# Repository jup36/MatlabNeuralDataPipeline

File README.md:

# MatlabNeuralDataPipeline
This repo contains the pipeline for Matlab neural data analysis. 
This repo aims to include all neural data analysis codes in applicable/generalizable forms.
Please see, the associated github repository, https://github.com/jup36/MatlabNeuralDataPipeline.git

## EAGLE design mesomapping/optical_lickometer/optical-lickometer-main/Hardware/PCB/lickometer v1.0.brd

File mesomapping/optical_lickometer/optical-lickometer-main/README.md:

## General description

This repository contains the design files for the assembly of a high-precision optical fiber based lickometer for mice.

----

## Features

* Fiber optic based lickometer
* Dual detection of licks and pokes
* TTL outputs
* Embedded poke LED 
* Support for a low profile solenoid valve
* RJ jack connector and screw terminal interface

----

## Folder structure

    .
    ├── Bonsai                  # Bonsai workflows
    ├── Hardware                # Design files
    │   ├── CAD                 # Mechanical design files, BOM and assembly instructions
    │   └── PCB                 # Schematic, layout and BOM of electronic board

----

## Licensing

License files can be found, and are applied to, each individual subfolder in this repository.

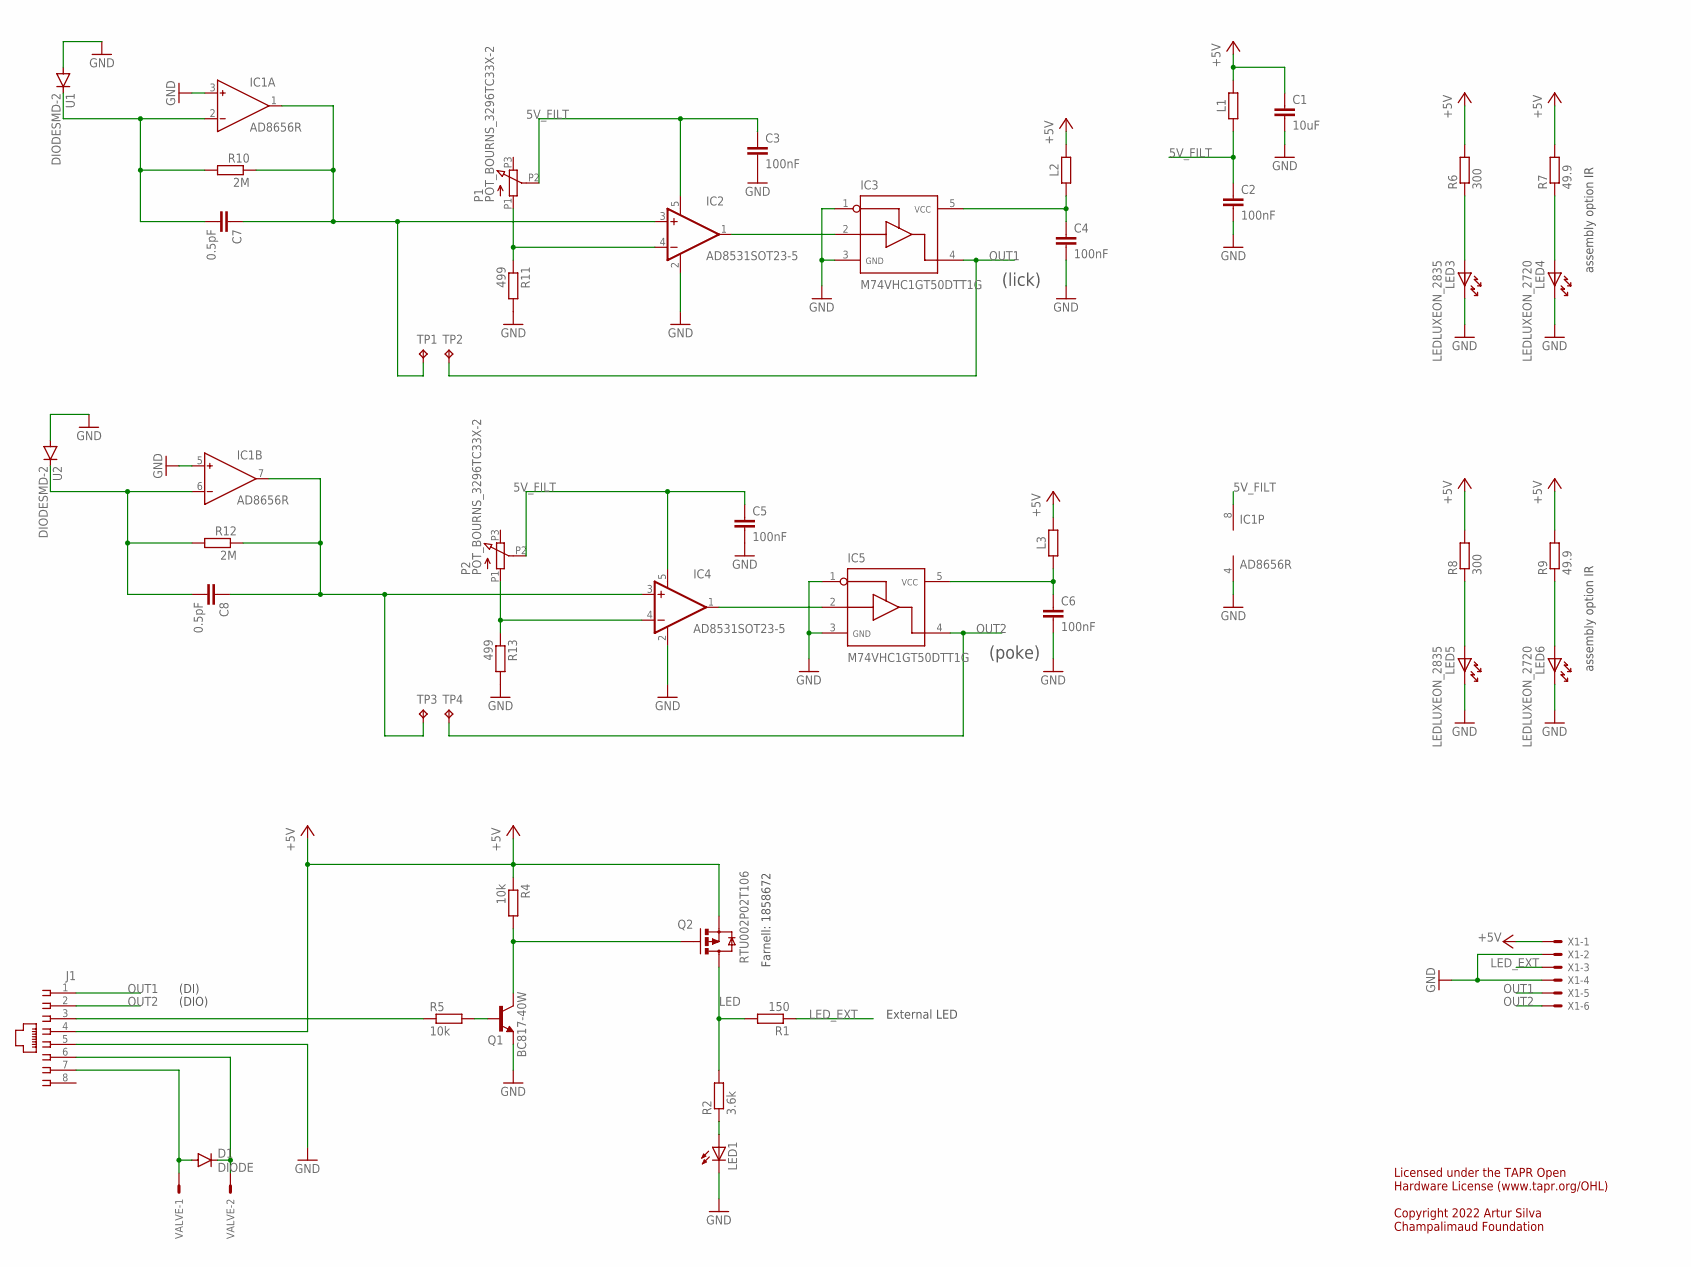
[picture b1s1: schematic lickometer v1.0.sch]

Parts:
C1: 10uF; C0603
C2, C3, C4, C5, C6: 100nF; C0402
C7, C8: 0.5pF; C0402
D1: DIODE; SOD-323-DIODE
IC1: AD8656R; SO8
IC2, IC4: AD8531SOT23-5; SOT23-5
IC3, IC5: M74VHC1GT50DTT1G; SOT23-5
J1: 215878-2
L1, L2, L3: 1k@100M; R0402
LED1: LED3MM
LED3, LED5: LEDLUXEON_2835; LED_LUXEON_2835
LED4, LED6: LEDLUXEON_2720; LED_LUXEON_2720
P1, P2: POT_BOURNS_3296TC33X-2; POT-TC33X-2
Q1: BC817-40W; SOT323-BEC
Q2: RTU002P02T106; SOT323
R1: 150; R0402
R2: 3.6k; R0402
R4, R5: 10k; R0402
R6, R8: 300; R0805
R7, R9: 49.9; R0805
R10, R12: 2M; R0402
R11, R13: 499; R0402
TP1, TP2, TP3, TP4: TPTP08SQ; TP08SQ
U1, U2: DIODESMD-2; SMD-2
VALVE: 22-23-2021
X1: 22-23-2061

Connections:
5V_FILT: C2.1, C3.1, C5.1, IC1.8 (V+), IC2.5 (V+), IC4.5 (V+), L1.2, P1.P2 (S), P2.P2 (S)
+5V: C1.1, J1.4, L1.1, L2.2, L3.2, Q2.1 (S), R4.1, R6.2, R7.2, R8.2, R9.2, X1.1
GND: C1.2, C2.2, C3.2, C4.2, C5.2, C6.2, IC1.3 (IN+), IC1.4 (V-), IC1.5 (IN+), IC2.2 (V-), IC3.1, IC3.3, IC4.2 (V-), IC5.1, IC5.3, J1.5, LED1.K (C), LED3.KATHODE (K), LED4.KATHODE (K), LED5.KATHODE (K), LED6.KATHODE (K), Q1.E, R11.2, R13.2, U1.A, U2.A, X1.2, X1.4
IN1: IC4.4 (-IN), P2.P1 (A), R13.1
IN2: IC2.4 (-IN), P1.P1 (A), R11.1
LED: Q2.3 (D), R1.2, R2.2
LED_EXT: R1.1, X1.3
unnamed: LED3.ANODE (A), R6.1
unnamed: C4.1, IC3.5, L2.1
unnamed: C7.2, IC1.2 (IN-), R10.2, U1.C
unnamed: D1.A, J1.7, VALVE.1
unnamed: D1.C, J1.6, VALVE.2
unnamed: IC2.1 (OUT), IC3.2
unnamed: J1.3, R5.1
unnamed: C7.1, IC1.1 (OUT), IC2.3 (+IN), R10.1, TP1.TP
unnamed: LED4.ANODE (A), R7.1
unnamed: IC4.1 (OUT), IC5.2
unnamed: C6.1, IC5.5, L3.1
unnamed: LED1.A, R2.1
unnamed: C8.2, IC1.6 (IN-), R12.2, U2.C
unnamed: C8.1, IC1.7 (OUT), IC4.3 (+IN), R12.1, TP3.TP
unnamed: LED5.ANODE (A), R8.1
unnamed: Q1.C, Q2.2 (G), R4.2
unnamed: Q1.B, R5.2
unnamed: LED6.ANODE (A), R9.1
OUT1: IC3.4, J1.1, TP2.TP, X1.5
OUT2: IC5.4, J1.2, TP4.TP, X1.6

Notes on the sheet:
External LED
Farnell: 1858672
Licensed under the TAPR Open Hardware License (www.tapr.org/OHL) Copyright 2022 Artur Silva Champalimaud Foundation
(lick)
(poke)
assembly option IR
(DIO)
(DI)

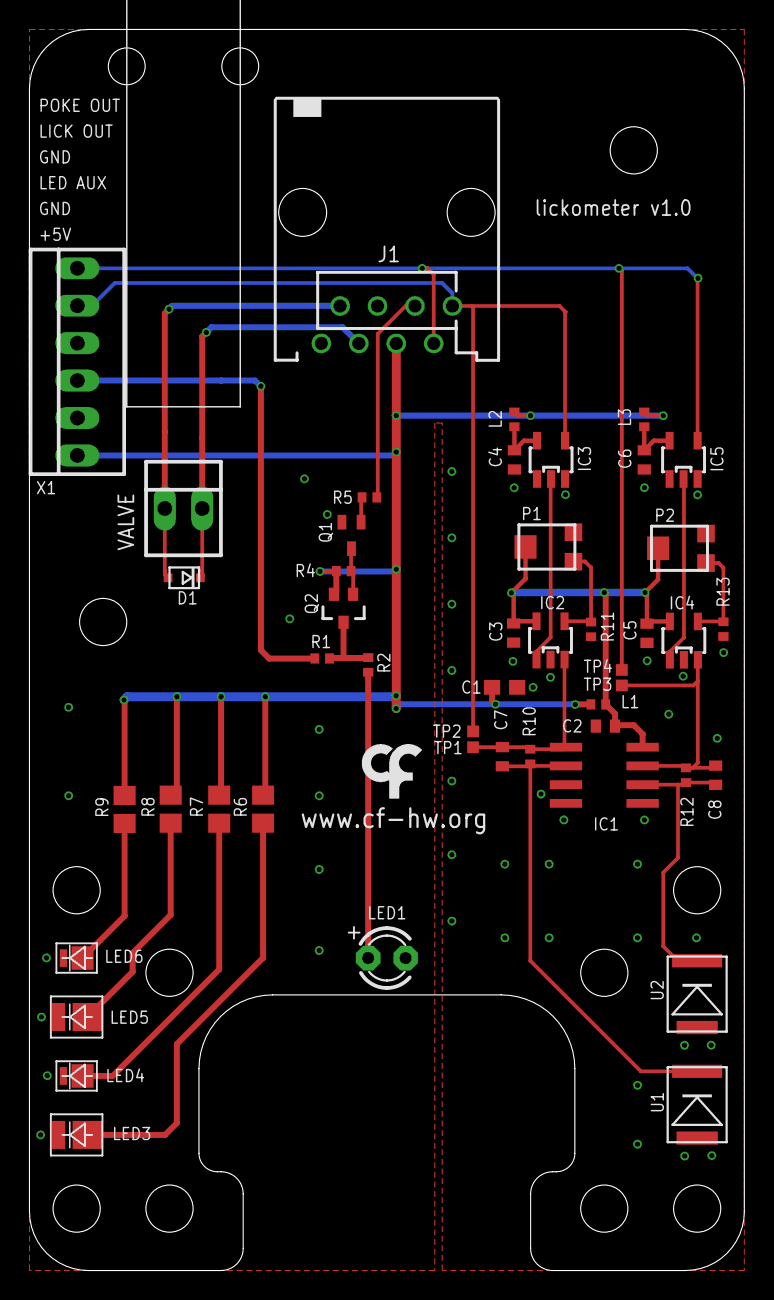
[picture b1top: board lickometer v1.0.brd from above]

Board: 2 copper layers, 48.5 x 84.2 mm, 49 parts (1 on the bottom side), 27 nets.

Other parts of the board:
U$1: LOGO_5
U$2: LOGO_7

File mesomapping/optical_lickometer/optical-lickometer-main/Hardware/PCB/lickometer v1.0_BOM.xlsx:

| Part(s) | Quantity | Description | Distributor | Part. No. | Price/Unit | Total Price
 | IC1 | 1 | OPAMP 28MHz 8/SOIC dual | Digikey | AD8656ARZ-REEL7 | 3.66 | 3.66
 | IC2, IC4 | 2 | OPAMP 3MHz SC70-5 | Mouser | AD8531AKSZ-REEL7 | 1.01 | 2.02
 | IC3, IC5 | 2 | Buffer single non-inverting TTL | Digikey | M74VHC1GT50DTT1G | 0.39 | 0.78
 | Q1 | 1 | Transistor BJT NPN SOT-23-3 | Mouser | 621-BC817-40W-7 | 0.27100000000000002 | 0.27100000000000002
 | Q2 | 1 | Transistor MOSFET P-channel SOT-323-3 20V 2.5A | Mouser | 621-DMP2165UW-7 | 0.38500000000000001 | 0.38500000000000001
 | D1 | 1 | Schottky diode 30V 1A SOD323 | Mouser | 621-SDM100K30L-7 | 0.438 | 0.438
 | P1, P2 | 2 | Trimmer 20kΩ 0.5W | Mouser | 652-TC33X-2-203E | 0.23599999999999999 | 0.47199999999999998
 | U1, U2 | 2 | PIN Photodiode SMT | Mouser | 720-SFH2200 | 0.95399999999999996 | 1.9079999999999999
 | R1 | 1 | Resistor SMD 150Ω ±1% 0402 | Mouser | 667-ERJ-2RKF1500X | 8.7999999999999995E-2 | 8.7999999999999995E-2
 | R2 | 1 | Resistor SMD 3,6kΩ ±1% 0402 | Mouser | 667-ERJ-2RKF3601X | 9.0999999999999998E-2 | 9.0999999999999998E-2
 | R7 (IR) | 1 | Resistor SMD 150Ω ±1% 0805 | Mouser | 667-ERJ-6RBD1500V | 0.155 | 0.155
 | R9 (IR) | 1 | Resistor SMD 49,9Ω ±1% 0805 | Mouser | 667-ERJ-6RED49R9V | 0.155 | 0.155
 | R11, R13 | 2 | Resistor SMD 499Ω ±1% 0402 | Mouser | 667-ERJ-2RKF4990X | 8.7999999999999995E-2 | 0.17599999999999999
 | R4, R5 | 2 | Resistor SMD 10kΩ ±1% 0402 | Mouser | 667-ERJ-2RKF1002X | 8.7999999999999995E-2 | 0.17599999999999999
 | R10, R12 | 2 | Resistor SMD 2MΩ ±1% 0402 | Mouser | 71-CRCW04022M00FKEDC | 8.7999999999999995E-2 | 0.17599999999999999
 | L1, L2, L3 | 3 | Ferrite bead 1kΩ 0402 | Mouser | 810-MMZ1005S102CT000 | 8.7999999999999995E-2 | 0.26400000000000001
 | C7, C8 | 2 | Capacitor ceramic 0.5pF 50V C0G/NP0 0402 | Mouser | 81-GRM1555C1HR50WA1D | 0.105 | 0.21
 | C2, C3, C4, C5, C6 | 5 | Capacitor ceramic 100nF 16V ±10% X7R 0402 | Mouser | GCM155R71C104KA55D | 8.7999999999999995E-2 | 0.43999999999999995
 | C1 | 1 | Capacitor ceramic 10uF 10V ±10% X5R 0603 | Mouser | 81-GRM188R61A106KE9D | 0.184 | 0.184
 | LED1 | 1 | LED white T-1 (3MM) | Mouser | 828-OVLAW4CB7 | 0.38500000000000001 | 0.38500000000000001
 | LED4, LED6 (IR) | 2 | Infrared LED 2720 940nm | Mouser | 997-L1IG094000000 | 2.2000000000000002 | 4.4000000000000004
 | VALVE | 1 | Terminal block 2P side entry 2.54mm | Mouser | 571-282834-2 | 1.58 | 1.58
 | J1 | 1 | Ethernet 8P8C top entry | Mouser | 571-55202594 | 1.56 | 1.56
 | X1 | 1 | Teminal block 8P side entry 2.54mm | Mouser | 571-282834-6 | 4.78 | 4.78
 |  | 1 | Printed Circuit Board | Seeedstudio |  | 5 | 5
 | Components | 40
 |  |  |  |  |  | Total | 22.200000000000003

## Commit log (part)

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2017-11-07 Matlab code to simulate a synfire chain network
    Synfire chain network:
    http://www.scholarpedia.org/article/Synfire_chains
    https://www.mathworks.com/matlabcentral/fileexchange/13802-synfire
    Pehlevan_Olveczky_2017
2018-02-21 SpikePreprocessing codes added
2018-02-22 SpikePreprocessing files updated 2/22/18
2018-03-09 adding behaviorTimestamps
2018-03-24 adding MVGC
2018-03-24 adding chronux
2018-03-24 adding multiple functions
2018-03-25 adding GC
2018-03-30 adding new joystick scripts/functions
2018-04-02 editing behaviorTimestamps.m
2018-05-01 update050118
2018-05-01 addingGPFA
2018-05-18 editing old joystick behavioral codes
2018-05-19 adding runGPFA.m getUnitOfHighXcorr.m
2018-07-10 adding fitrm_ranova_multcompare.m
2018-07-26 .adding a bunch of codes
2018-07-26 .adding JRCLUST
2018-07-26 .adding a bunch
2018-07-26 reorganizing the folder
2018-07-26 adding tonic-master
2018-07-26 adding joystickCodes
2018-08-03 editing corrNeuralTrajMovKinematics
2018-08-17 updating from parkj mac
2018-08-23 adding VTA_Cell_classification_to_AGB
2018-08-23 adding func_GMM to VTA_Cell_classification
2018-09-04 adding miscellaneous changes
2018-09-04 small change in behaviorTimestamps.m
2018-09-06 up-to-date ver. before making changes in PSTH_raster and its subfunctions.
2018-09-12 adding spikeSorting auxiliary
2018-09-16 adding behaviorCode for AGB
2018-09-24 just a regular commit
2018-10-10 adding js2.0_Beh
2018-10-29 a bunch of updates
2018-11-02 updating Js2.0 trajectory analysis codes
2018-11-07 updating js2.0 from labbenchmachine
2018-11-12 updating js2.0_Beh from labBench machine
2018-11-12 updating jsBeh2.0 from the lab bench machine
2018-11-16 updating Js2.0 codes from mac
2018-11-20 updating js2.0_Beh from the lab bench PC
2018-11-28 update from lab bench machine
2018-11-29 Important js2.0 code updates including vidoe file process from LabBenchMachine
2018-11-30 updating jsVideoProcess.m from lab bench machine
2018-12-06 updating from labbench PC
2018-12-12 updating from laptop
2019-01-29 updating from the lab bench machine
2019-02-26 update from myrig
2019-03-04 Create getHH3geom
2019-03-04 Create PSTH_rasters_Cg
2019-03-04 Create parse_input_psth_Cg
2019-03-04 updating from the lab bench
2019-03-06 Update behaviorTimestampsJsWrapper.m from myRig
2019-03-06 updating from the labBench
2019-03-06 updating from labBench
2019-03-09 Update PSTH_rasters.m
    Addition of reward PSTHs no-stim trials only.
    Saving spikeTimes cells.
2019-03-12 update from myRecordingRig
2019-04-10 paser_input_Js updated
2019-04-10 updatedFromMyRig
2019-04-10 updating behaviorTimeStampsJsWrapper
2019-04-11 updating JsVideoFileOrganizer
2019-04-11 updating behaviorTimestampsJs
2019-04-11 updating behaviorTimestampsJs.m
2019-04-15 updating from myMac
2019-04-15 JsVideoFileOrganizer
2019-04-15 commiting JsVideoFileOrganizer
2019-04-30 Editing behaviorTimestampsJs on 4/30/19
2019-05-01 Editing behaviorTimestampsJs on 5/1/19
2019-06-07 updating from myRig
2019-07-31 updating from my mac
2019-08-14 Adding cgStimEffectAnalysisJsTrj.m
2019-08-20 updating behaviorTimestampsJs.m from my Rig'
2019-09-10 updating changes from the labBench
2019-09-10 updating from my labtop
2019-10-29 update from my laptop
2019-10-29 updating from labbench mostly hand trajectory preprocessing stuffs
2019-10-30 updating handtrajectory stuffs from labBench machine
2019-11-02 update from labBench
2019-11-02 update from myRig on videoHandTrajAnalysis
2019-11-05 update from the labBench
2019-11-07 update from Mac
2019-11-08 updating at labBench
2019-11-12 updating from labBench for 'getReachTimesJs2p0.m'
2019-11-12 updating from labBench; hand trajectory + glm codes
2019-11-21 updates from my laptop
2019-12-04 updates from Macmostly for glm codes
2019-12-12 updating from my laptop
2020-02-10 updating from labBench machine to labBench
2020-05-12 updating from myRig'
2020-05-15 adding codes NP evaluation tools from Jennifer
2020-10-05 updating trjDecoder
2021-01-14 update from my labBench
2021-01-22 updating labBench
2021-05-07 update from my mac'
2021-05-13 update from myRig to remote
2022-05-19 adding some of the new files from labBench
2023-06-14 commit from my MacBook 6/14/23
2023-06-20 updating behaviorTimestampsPP
2023-09-12 adding neural_encoding_trial_types_js2p0
2023-11-01 Committing deleted file
2023-11-20 updating from lab pc
2024-02-02 updating from BuschmanlabNeuropixel
2024-04-23 updating from NP machine
2024-08-20 updating from my laptop 082024
2024-10-16 updating from buschmanNP284
2024-12-06 commiting from my laptop
2024-12-06 committing from my laptop
2025-02-05 commitfrom my laptop
2026-04-13 updating from oldNP
